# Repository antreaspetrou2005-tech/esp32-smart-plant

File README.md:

# 🌱 ESP32 Smart Plant Monitoring System

An IoT-based smart plant monitoring and automatic watering system built using an ESP32.

The system monitors environmental and soil conditions in real time, displays the measurements locally and through a web dashboard, and automatically waters the plant when the soil becomes dry.

---

## 📋 Features

- 🌡 Temperature and humidity monitoring using DHT11
- 🌱 Soil moisture monitoring
- 💧 Automatic watering based on soil moisture level
- 📺 Real-time OLED display
- 🌐 Wi-Fi web dashboard
- 🔘 Manual watering through the web interface
- 🔌 Relay-controlled water pump
- 🛠 Custom-built DC water pump
- 🖥 Custom PCB designed in KiCad

---

## ⚙️ How It Works

The ESP32 continuously reads data from the temperature, humidity, and soil moisture sensors.

When the soil moisture drops below the defined threshold, the ESP32 activates the relay, which powers the water pump.

Sensor readings and system status are displayed on both the OLED screen and the Wi-Fi web dashboard.

**System flow:**

`Sensors → ESP32 → Control Logic → Relay → Water Pump`

`ESP32 → OLED Display + Web Dashboard`

---

## 🛠 Hardware

- ESP32 DevKit V1
- DHT11 Temperature & Humidity Sensor
- Soil Moisture Sensor
- SSD1306 OLED Display
- Relay Module
- Custom-built DC Water Pump
- Custom PCB

---

## 💻 Software

- Arduino IDE
- KiCad 10
- ESP32 Web Server

---

## 🔧 Working Prototype

The complete system was first assembled and tested on a breadboard before moving to the custom PCB design.

---

## 📺 OLED Display

The OLED provides real-time information including temperature, air humidity, soil moisture, pump status, and plant watering status.

---

## 💧 Custom-built DC Water Pump

Instead of using a ready-made water pump, a small DC water pump was built from scratch for the project.

The pump uses a DC motor, a custom-made impeller, and a handmade housing with inlet and outlet connections.

It is controlled by the ESP32 through a relay and can be activated automatically when the soil moisture level is low.

---

## 📐 Schematic

The complete circuit schematic was designed in KiCad.

---

## 🖥 PCB Layout

A custom PCB was designed to integrate the ESP32 and the system's sensors and peripherals.

---

## 📦 3D PCB View

3D visualization of the custom PCB design.

---

## 🌐 Web Dashboard

The ESP32 hosts a local web interface that allows real-time monitoring of the plant and manual activation of the watering system.

---

## 📁 Repository Structure

- `firmware/` → ESP32 source code
- `pcb/` → KiCad schematic and PCB design files
- `gerber/` → PCB manufacturing files
- `images/` → Project images and screenshots

---

## 🚀 Current Status

- ✅ Breadboard prototype completed
- ✅ Sensors successfully integrated
- ✅ OLED interface completed
- ✅ Wi-Fi web dashboard completed
- ✅ Automatic watering system working
- ✅ Custom water pump built and tested
- ✅ Firmware completed
- ✅ PCB designed in KiCad
- ✅ Gerber manufacturing files generated
- ⏳ Physical PCB manufacturing and assembly coming soon

---

## 👨‍💻 Author

**Antreas Petrou**

Electrical Engineering Student  
Aristotle University of Thessaloniki

---

## 📄 License

This project is licensed under the MIT License.

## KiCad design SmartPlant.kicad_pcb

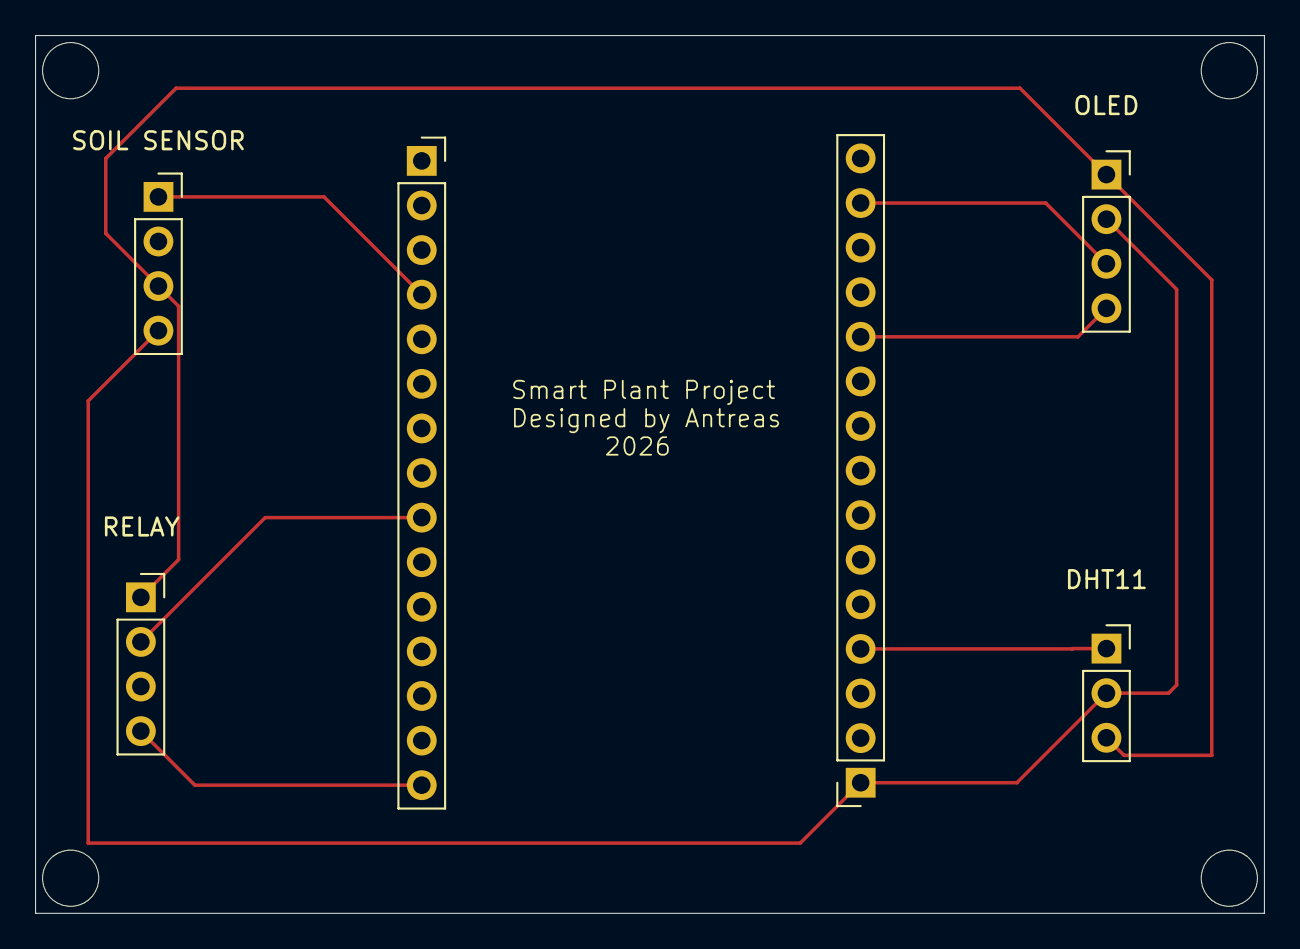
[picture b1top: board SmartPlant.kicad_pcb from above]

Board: 2 copper layers, 70.0 x 50.0 mm, 6 parts (0 on the bottom side), 8 nets.

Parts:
DHT11 : PinSocket_1x03_P2.54mm_Vertical
OLED : PinSocket_1x04_P2.54mm_Vertical
RELAY : PinSocket_1x04_P2.54mm_Vertical
SOIL SENSOR : PinSocket_1x04_P2.54mm_Vertical
U1, U2: PinSocket_1x15_P2.54mm_Vertical

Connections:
+3V3: DHT11.2 (+), OLED.2 (VCC), SOIL SENSOR.4 (VCC), U2.1 (3V3)
+5V: RELAY.4 (VCC), U1.15 (VIN)
<NO NET>: DHT11.3 (-), OLED.1 (GND), RELAY.1 (GND), SOIL SENSOR.3 (GND)
D2: DHT11.1 (DATA), U2.4 (D2)
D21: OLED.4 (SDA), U2.11 (D21)
D22: OLED.3 (SCL), U2.14 (D22)
D26: RELAY.2 (IN1), U1.9 (D26)
D34: SOIL SENSOR.1 (A0), U1.4 (D34)
